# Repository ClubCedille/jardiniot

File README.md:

# JardinIoT
Le projet JardinIoT est un jardin autonome. Ce jardin est composé de "buckets" autonomes dans lesquels les plantes sont semées. Un bucket comporte plusieurs sondes mesurant, entre autres, la température et l'humidité. Le bucket, à l'aide du serveur, ajuste l'humidité de la terre, la température et la lumière que reçoit la plante en se basant sur les données reçues par les sondes ainsi que sur différents facteurs, tels l'heure du jour et la date.

Plus de détails sur le projet peuvent être trouvés sur [le Wiki](https://github.com/ClubCedille/jardiniot/wiki "Wiki JardinIoT").

Le projet [a remporté un OCTAS](https://etsmtl.ca/nouvelles/2018/Gala-des-OCTAS-2018) dans la catégorie 'Relève étudiante' lors du Gala des OCTAS en 2018.

## Instructions d'installation du système embarqué

1. Vérifiez votre version de Python afin que ce soit la version 2.7 (`python --version`)
2. Installez PlatfromIO à l'aide de `pip`: `pip install -U wheel semantic-version platformio`. Il se peut que vous deviez utiliser `pip2` si Python 3 est installé sur votre ordi.
3. Clonez le projet: `git clone https://github.com/ClubCedille/jardiniot.git`
4. Vous devez installer chaque dépendence (les `lib_deps` qui sont trouvées dans `platformio.ini`) pour que le code puisse compiler:
	* Allez dans `jardiniot-emb/esp/` et exécutez cette commande: `platformio lib install "EspSoftwareSerial" "WiFi" "PubSubClient" "WifiManager" "CmdMessenger"`
	* Allez dans `jardiniot-emb/arduino/` et exécutez cette commande: `platformio lib install "StandardCplusplus" "Timer" "Adafruit Unified Sensor" "DHT sensor library"`
5. Pour flasher le Arduino avec le code, allez dans le fichier `arduino` et exécutez la commande `platformio run --target upload`.
	* Si jamais le logiciel ne peut pas accéder à `/dev/ttyACM0`, il faut faire: `sudo chmod 666 /dev/ttyACM0`.
6. Allez dans le fichier `esp` et faites la même commande pour flasher le ESP8266. Connectez qu'un seul truc à flasher à la fois sur l'ordi.
7. Pour recevoir des `Serial.print()` du Arduino, vous pouvez le faire avec cette commande: `platformio device monitor -p /dev/ttyACM0 -b 9600`

Ceci est un guide général et les commandes peuvent changer. Allez lire [la doc](http://docs.platformio.org/en/latest/installation.html) pour plus de détails.

## Instructions pour démarrer la partie serveur

L'application utilise les ports suivants pour son fonctionnement:

- `1883` pour MQTT
- `5000` pour l'API du site Web
- `8080` pour le site Web

Le port de l'API est hardcodé dans le frontend et n'est donc pas configurable lors du build.

### Avec Docker Compose

Prérequis:

- Docker avec Docker Engine > 17.12.0
- Docker Compose > 1.21 (pour supporter "Compose file" version 2.4)

Pour rouler:

```bash
# docker-compose up
```

Le site est accessible au <http://localhost:4000/>, contrairement au port `8080` mentionné précedemment.

Le site est accessible sur le port `4000` lorsque la commande `docker-compose` est utilisée, alors que si l'application est démarrée manuellement le port `8080` sera utilisé.

### Sans Docker Compose

*TODO*

<!---
[//]: # (Pour utiliser l'application sans docker-compose, la procédure est plus complexe.)

[//]: # (Le backend et le frontend sont indépendant, donc il est possible de construire/arrêter l'un sans briser l'autre)
-->

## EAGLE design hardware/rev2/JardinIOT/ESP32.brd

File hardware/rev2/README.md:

# Matériel JardinIOT révision 2.0

## Contexte :

L'arrivé de nouveaux modules plus performants sur le marché des systèmes
embarqués a rendue le matériel utilisé dans la dernière révision obsolète. 
Utiliser ce nouveau matériel permettraient de réduire les irritants et les
problèmes qu'avait la dernière version de JardinIOT.

## Objectifs :

Voici les objectifs pour la révision matériel 2.0 du projet JardinIOT.

* Réduire le nombre de contrôleurs différents dans le projet.
* Réimplémenter le code des itération précédentes pour qu'il fonctionne avec un
  contrôleur possédant plus de RAM (e.g ESP32, Arduino Due/MEGA, Rasperry Pi, etc...).
* Produire un circuit imprimé pour éviter les couettes et les mottes de fils.
  Bref, donner une allure plus professionnelle et moins "prototype" au projet.
* Uniformiser la source de tension. L'itération précédente devait être branché à
  2 places différentes pour leur alimentation.
  
## Choix: 

* Logiciel de dessin pour les circuits: Autodesk EAGLE. Rationnel: Je me suis
  familiarisé avec ce logiciel en technique et m'y sens à l'aise. De plus, le
  logiciel est gratuit pour les étudiants à la création d'un compte Autodesk.
  
* Nouveau contrôleur, plusieurs choix disponibles avec plusieurs implications:

| Possibilité  | pour                                         | contre                                                     |
|--------------|----------------------------------------------|------------------------------------------------------------|
~~| Rasperry pi  | Beaucoup de mémoire                          | * Tension d'opération incompatible avec les anciens capteurs |~~
| ESP32        | Mémoire suffisante                           | * Tension d'opération incompatible avec les anciens capteurs * Peu de GPIO|
~~| Arduino Mega | Moins de mémoire que les options précédentes | * Tension d'opération compatible avec les anciens capteurs   |~~

~~Il est important de mentionner qu'il est possible d'acquérir des nouveaux~~
~~capteurs pour accomoder les différents choix. De plus, il existe aussi des~~
~~multiplexeurs de GPIO dans le cas ou on désire continuer avec l'option ESP32.~~

## Journal de bord

Modification 20/03/2020:
- Écriture barré pour ce que ne s'applique plus.

Après quelques heures de recherche, il est devenu évident que les capteurs déjà utilisés
pouvaient être conservés car la tension d'opération du ESP32 est compatible. Le capteur en
question est le DHT22. Ce capteur peut opérer à 3.3v tout comme à 5v. Pour les
lumières, il sera très peu coûteux des les interfacer avec un transistor de
puissance.

Le ESP32 semble être de plus en plus le meilleur candidat. De plus,il existe un [trousseau de
dévelopement]https://docs.espressif.com/projects/esp-idf/en/v4.0/) de la
compagnie Espressif qui a produit le module. Les APIs et le matériel y sont très bien documentés.

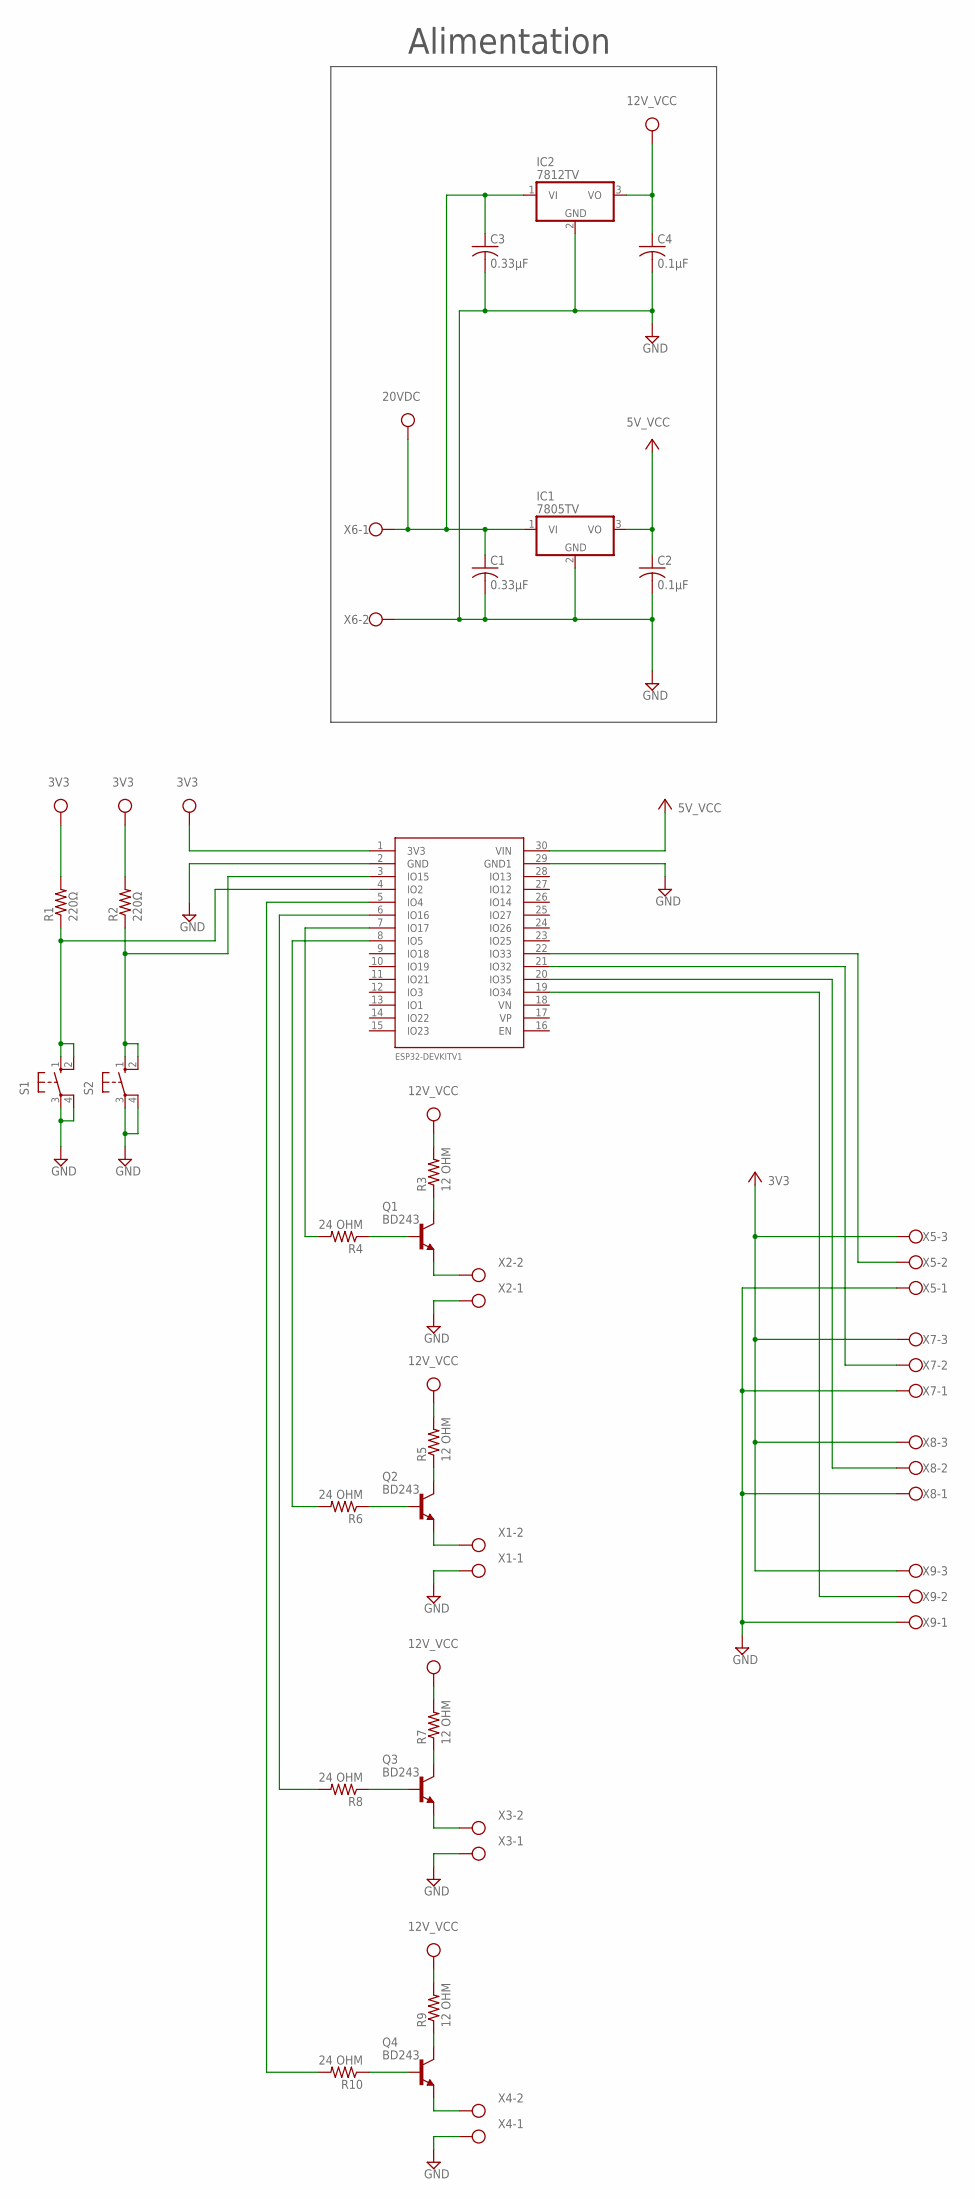
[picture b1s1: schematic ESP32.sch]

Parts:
C1, C3: 0.33µF; C0805
C2, C4: 0.1µF; C0805
IC1: 7805TV; TO220V
IC2: 7812TV; TO220V
Q1, Q2, Q3, Q4: BD243; TO220
R1, R2: 220Ω; 0204/5
R3, R5, R7, R9: 12 OHM; 0204/7
R4, R6, R8, R10: 24 OHM; 0204/7
S1, S2: 10-XX; B3F-10XX
U$1: ESP32DEVKITV1; ESP32-DEVKITV1
X1, X2, X3, X4, X6: W237-102
X5, X7, X8, X9: W237-103

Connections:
3V3: R1.2, R2.2, U$1.1 (3V3), X5.3, X7.3, X8.3, X9.3
5V_VCC: C2.1, IC1.3 (VO), U$1.30 (VIN)
12V_VCC: C4.1, IC2.3 (VO), R3.2, R5.2, R7.2, R9.2
20VDC: C1.1, C3.1, IC1.1 (VI), IC2.1 (VI), X6.1
GND: C1.2, C2.2, C3.2, C4.2, IC1.2 (GND), IC2.2 (GND), S1.3, S1.4 (P1), S2.3, S2.4 (P1), U$1.2 (GND), U$1.29 (GND1), X1.1, X2.1, X3.1, X4.1, X5.1, X6.2, X7.1, X8.1, X9.1
unnamed: R1.1, S1.1 (S), S1.2 (S1), U$1.4 (IO2)
unnamed: Q1.3 (E), X2.2
unnamed: R2.1, S2.1 (S), S2.2 (S1), U$1.3 (IO15)
unnamed: Q1.2 (C), R3.1
unnamed: Q1.1 (B), R4.1
unnamed: Q2.3 (E), X1.2
unnamed: Q2.2 (C), R5.1
unnamed: Q2.1 (B), R6.1
unnamed: Q3.3 (E), X3.2
unnamed: Q3.2 (C), R7.1
unnamed: Q3.1 (B), R8.1
unnamed: Q4.3 (E), X4.2
unnamed: Q4.2 (C), R9.1
unnamed: Q4.1 (B), R10.1
unnamed: R4.2, U$1.7 (IO17)
unnamed: U$1.22 (IO33), X5.2
unnamed: R8.2, U$1.6 (IO16)
unnamed: R6.2, U$1.8 (IO5)
unnamed: R10.2, U$1.5 (IO4)
unnamed: U$1.21 (IO32), X7.2
unnamed: U$1.20 (IO35), X8.2
unnamed: U$1.19 (IO34), X9.2

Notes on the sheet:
Alimentation

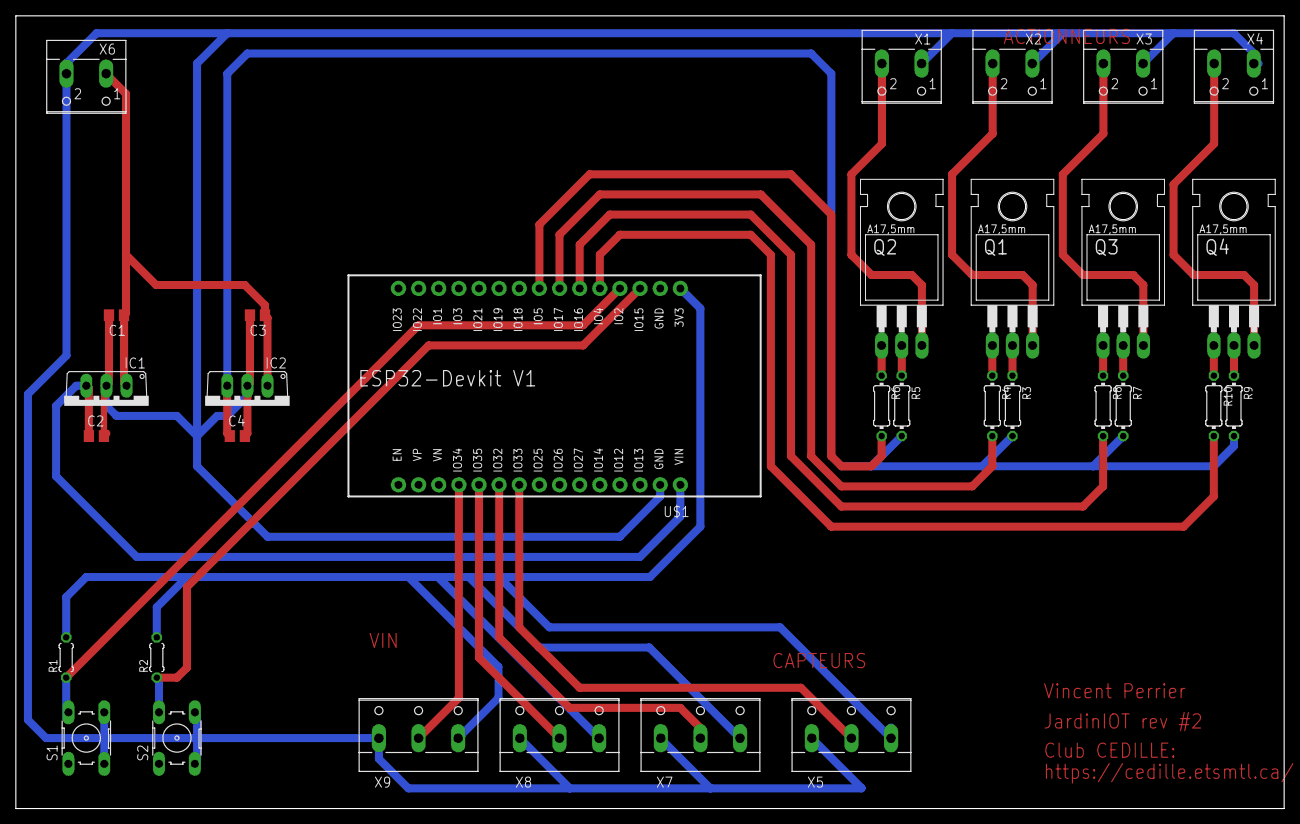
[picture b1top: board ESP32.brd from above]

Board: 2 copper layers, 160.0 x 100.0 mm, 32 parts (0 on the bottom side), 27 nets.

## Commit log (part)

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2017-01-21 Copie du serveur web
2017-02-21 Projet(s) qui compile(nt) sans erreur
2017-03-03 Lecture des données du DHT
2017-03-04 Modifié les fichiers READMEs
2017-03-06 Commit avant de faire un test d'envoie de données au ESP et de renvoi
2017-03-06 Imported from https://mikefaille@github.com/ClubCedille/jardiniot.git
2017-03-28 Ajout du code de l'API + modification du README
2017-04-03 On peut pas changer le nom de la topic avec String.c_str()
2017-04-07 Esthétisme
2017-05-05 L'API utilise maintenant une base de données au lieu de données stub.
    -En ce moment, le backend BD est SQLite. On est passé de PostgreSQL à SQLite parce que le serveur PostgreSQL de dev est down.
    -Éventuellement, on pensait peut-être implémenter un ORM au lieu de dépendre d'un backend en particulier (voir Sequelize et/ou autres ORM Node.js)
    -Je n'ai pas implémenté l'ORM right now, puisqu'on cherche à avoir un prototype fonctionnel le plus tôt possible. Donc j'ai décidé d'utiliser SQLite pour le moment. Je vais créer un issue.
    -Vu que le backend de BD a changé, le connecteur qui fait le lien entre le serveur MQTT et la BD est obsolète, je vais le réécrire dans les heures qu
2017-05-07 début du code pour api vers esp
2017-05-07 Remove connector.js
2017-05-09 Ajout du code dans le connecteur pour envoyer des commandes à l'ESP. Reste à gérer les requêtes POST dans l'API
2017-05-12 add yarn install guide
2017-05-12 Changé les requêtes SQL pour des statements préparés. Aussi ajouté des constantes de limites.
2017-05-15 Communication entre esp et arduino fonctionnel
2017-05-19 Enlever le code mort et ajout de commentaires
2017-06-06 Peaufinage code
2017-06-09 Ajout de express, pas encore testé sur la bd
2017-06-23 Mise à jour des différents senseurs avec les nouvelles valeurs reçues
2017-07-07 Fix fonction readInfoFromEsp
2017-07-08 Librarie Timer enlevée et ajoutée aux dépendances
2017-07-08 Nettoyage du repo
2017-07-28 Fix mqtt pas sur 127.0.0.1 + update readme
2017-11-27 Début de l'intégration des ventillateurs dans le système
2017-12-11 Fix memory leak
2017-12-22 Restructure de main.cpp
2018-01-22 Utilisation de yarn pour les modules & installation bootstrap
2018-01-28 styling header
2018-02-02 Réparation d'un bug où un moteur n'était pas trouvé
    Merci @AlexBrochu pour avoir pointé le bug
2018-02-02 Modification de la fonction de test
2018-02-04 Footer enligné + README update
2018-02-25 Ajout de la solution pour compiler si pas accès à /dev/ttyACM0
2018-02-26 Le check d'OS a été enlevé du script de doc
    Le script fonctionnait bien sur Manjaro aussi
2018-02-26 Le lien de la doc du code source est mis plus visible
2018-03-01 DHT fonctionnel
2018-03-04 Setup the hardware folder and starting part gration.
2018-03-11 Ajout d'un projet CodeBlocks
2018-03-14 Ajout copyright et coherence space/tabs
2018-03-22 Ajout de quelques vérifications pour les commandes reçues
2018-03-28 Ajoute d'une seed pour la DB sqlite
2018-04-15 Implémente BucketService pour lister les buckets.
    Ce commit contient plusieurs changements:
    - Implémentation d'un service HTTP qui fait des requêtes sur l'API
    - Ajoute de l'affichage de la liste des buckets recouvert par le service
    dans l'écran d'accueil
    Pour le moment, il y a plusieurs trucs d'hardcodé. C'est un WIP et un
    premier succès au niveau des appels à l'API. :)
2018-04-20 Added Xs for N/C pins.
2018-04-24 Added yarn-error.log and node_modules to gitignore
2018-05-06 Separation de bucket et bucket-detail par routage et ajout du bucketdetailservice
2018-05-08 indentation a 4 espaces dans sqliteconnector
2018-05-08 affichage des donnes dans bucket/:id
2018-05-22 ajout d'une bibliothèque manquante
2018-06-03 Implémentation de delay()
2018-06-04 Implémentation de la fonction millis() du Arduino
2018-06-13 Premiere apparition des data des capteurs dans la vue BucketDetails
2018-06-17 Parametrage de l'adresse a laquel se situe l'api
2018-06-17 Modifie la route /bucket/:id/sensor/:id pour etre cohérent avec le README
2018-06-17 Mise à jour du README du panneau de contrôle
2018-06-22 'espval' doit être vidé pour pas que les messages s'accumulent dedans
2018-07-01 Ajout de fonctions du Arduino pour que le DHT original compile entièrement
2018-07-03 Correction du freeze avec tous les senseurs en remplaçant les char*
    Merci à @ioioioio qui a trouvé le bug. Explication: https://rocketchat.cedille.club/channel/projet_jardiniot?msg=aBeGXfnDdAojvWkqT
2018-07-08 Changement de structure pour réduire les instructions au précompilateur
2018-07-12 Déplament du dossier arduinolayer
2018-07-12 Il ne reste des ifdef que dans main
2018-08-14 Fix la liste
2018-08-15 Ajout de la sauvegarde des données vers une base de données
2018-08-16 Ajoute de l'entete GLP3 ou ce n'était pas fait
2018-09-11 Ajout des permissions 'run' aux fichiers .sh
2018-09-12 Fix exception à cause des différents threads
    Database error: SQLite objects created in a thread can only be used in that same thread
2018-09-12 Fix: On affichait 2 fois la température et pas l'humidité dans le JSON
2018-09-29 Génération de commandes et contrôle des ventilateurs
2018-10-06 Endpoint /bucket/id pour faire une update
    - Permet d'updater les informatoins du jardin
2018-10-27 Configure build pour utiliser pipenv (#7)
    * Configure build pour utiliser pipenv
    Pipenv est le successeur de virtualenv.
    Il combine pip et virtualenv ensemble.
    * Le fichier Pipfile.lock est mis dans le .gitignore
2018-10-27 Fix erreur dans 'run.sh' qui faisait qu'un fichier '1' était créé à chaque fois que le script était roulé
2019-01-20 Indente "bucket.py" avec des "Tabs"
2019-01-20 React frontend added.
2019-01-20 Fix more SQLIs
2019-01-20 Fix even more SQLIs
2019-01-20 Fix 'TypeError: must be str, not list'
2019-01-20 css changes, not done
2019-01-27 Lights, Fans and design are all done.
2019-01-27 Vieux API enlevé
2019-01-27 Add .gitignore
    .db and .pyc are bothering
2019-01-27 Notice importante pour taille d'allocation
2019-02-14 Revert "MAJ README du serveur web"
    This reverts commit 3de6a8768373657de244cd22fb53937ec896ecb5.
2019-02-17 Renomme frontend-web-v2 -> frontend-web
2019-02-18 Update le docker-compose pour inclure le frontend
    - Restreint les ports _exposed_ sur le host
    - Ajoute un `healthcheck` pour l'API
    - Ajoute un `restart` aux containers pour redémarrer en cas de crash
2019-02-28 Renomme mqttmain.py~HEAD à mqttmain.py
2019-03-05 Modifie le reseau docker-compose pour exposer les ports sur l'hôte
2019-03-07 Renommé la variable 'composeR' qui s'appelle maintenant 'composer'.
2019-05-08 Ajoute la documentation pour run avec Docker Compose
    La documentation pour rouler l'application sans Docker Compose est à
    venir.
2019-06-27 RIP ancien Front-End Web de Roch
2019-07-01 Update la documentation du frontend concernant le Dockerfile
2020-03-12 Bougé tous les fichiers des révisions précédentes dans hardware/rev1
2020-03-13 Fix de quelques typos
2020-03-20 Changement d'emplacement de fichiers pour le code source du contrôleur
2020-03-23 Création d'un repetoire de début de projet esp-idf
2020-03-23 fix de config.h
2020-03-27 DConversion des types arduino en types standards.
2020-05-01 Ajout des borniers à vis pour les capteurs et actionneurs
2020-05-01 ajout du module config et GPIOstrategy
2020-05-02 Travail sur les fonctionnalité de la config wifi
2020-05-02 fix le build
2020-05-03 Debut d'implementation d'un GPIOstrategy pour le ESP32
2020-05-12 création du module esp32gpio
2020-05-12 travail sur GPIO strategy
2020-05-12 Changement des espacement du symbol '*' pour se conformer à la convention de code
2020-05-12 rouller --> rouler
2020-05-12 Add missing keyword docker
2020-05-12 Remove cache
2020-05-12 Enlevé la vagrantfile, ce n'est pas d'importance tout de suite
2020-05-13 Test commands and work dir
2020-05-13 Fix work dir
2020-05-13 Changement d'indentation, fix d'espaces de trop dans Readme.md, fix des dates dans les headers gpl
2020-05-13 Fixups
2020-05-13 test apt
2020-05-13 more tests
2020-05-13 Cleaner unit tests
2020-05-13 remove pipenv
2020-05-13 Restore py script + setup into config.yml
2020-05-13 Mise à jour du orb
2020-05-13 changement du fichier format.sh. Le script est plus clean
2020-05-14 Ajout du script de circle CI à la branche hardware
2020-05-27 Applied autopep8
2020-06-10 Fixed stuff again
2020-06-10 Bump sshpk from 1.13.0 to 1.16.1 in /serveur-web
    Bumps [sshpk](https://github.com/joyent/node-sshpk) from 1.13.0 to 1.16.1.
    - [Release notes](https://github.com/joyent/node-sshpk/releases)
    - [Commits](https://github.com/joyent/node-sshpk/compare/v1.13.0...v1.16.1)
2020-06-10 Bump mixin-deep from 1.3.1 to 1.3.2 in /serveur-web (#101)
    Bumps [mixin-deep](https://github.com/jonschlinkert/mixin-deep) from 1.3.1 to 1.3.2.
    - [Release notes](https://github.com/jonschlinkert/mixin-deep/releases)
    - [Commits](https://github.com/jonschlinkert/mixin-deep/compare/1.3.1...1.3.2)
2020-06-10 Bump sshpk from 1.13.0 to 1.16.1 in /serveur-web (#99)
    Bumps [sshpk](https://github.com/joyent/node-sshpk) from 1.13.0 to 1.16.1.
    - [Release notes](https://github.com/joyent/node-sshpk/releases)
    - [Commits](https://github.com/joyent/node-sshpk/compare/v1.13.0...v1.16.1)
2020-06-10 Bump mqtt-packet from 5.3.0 to 5.6.1 in /serveur-web
    Bumps [mqtt-packet](https://github.com/mqttjs/mqtt-packet) from 5.3.0 to 5.6.1.
    - [Release notes](https://github.com/mqttjs/mqtt-packet/releases)
    - [Commits](https://github.com/mqttjs/mqtt-packet/compare/v5.3.0...v5.6.1)
2020-06-10 Bump mqtt-packet from 5.3.0 to 5.6.1 in /serveur-web (#103)
    Bumps [mqtt-packet](https://github.com/mqttjs/mqtt-packet) from 5.3.0 to 5.6.1.
    - [Release notes](https://github.com/mqttjs/mqtt-packet/releases)
    - [Commits](https://github.com/mqttjs/mqtt-packet/compare/v5.3.0...v5.6.1)
2020-06-10 Efface vieux fichiers de dépendances du serveur web JS
2020-06-10 Bump handlebars from 4.0.11 to 4.7.6 in /frontend-web-v2 (#107)
    Bumps [handlebars](https://github.com/wycats/handlebars.js) from 4.0.11 to 4.7.6.
    - [Release notes](https://github.com/wycats/handlebars.js/releases)
    - [Changelog](https://github.com/handlebars-lang/handlebars.js/blob/master/release-notes.md)
    - [Commits](https://github.com/wycats/handlebars.js/compare/v4.0.11...v4.7.6)
2020-06-10 Bump merge from 1.2.0 to 1.2.1 in /frontend-web-v2
    Bumps [merge](https://github.com/yeikos/js.merge) from 1.2.0 to 1.2.1.
    - [Release notes](https://github.com/yeikos/js.merge/releases)
    - [Commits](https://github.com/yeikos/js.merge/compare/v1.2.0...v1.2.1)
2020-07-07 Bump npm from 6.4.0 to 6.14.6 in /frontend-web-v2
    Bumps [npm](https://github.com/npm/cli) from 6.4.0 to 6.14.6.
    - [Release notes](https://github.com/npm/cli/releases)
    - [Changelog](https://github.com/npm/cli/blob/latest/CHANGELOG.md)
    - [Commits](https://github.com/npm/cli/compare/v6.4.0...v6.14.6)
